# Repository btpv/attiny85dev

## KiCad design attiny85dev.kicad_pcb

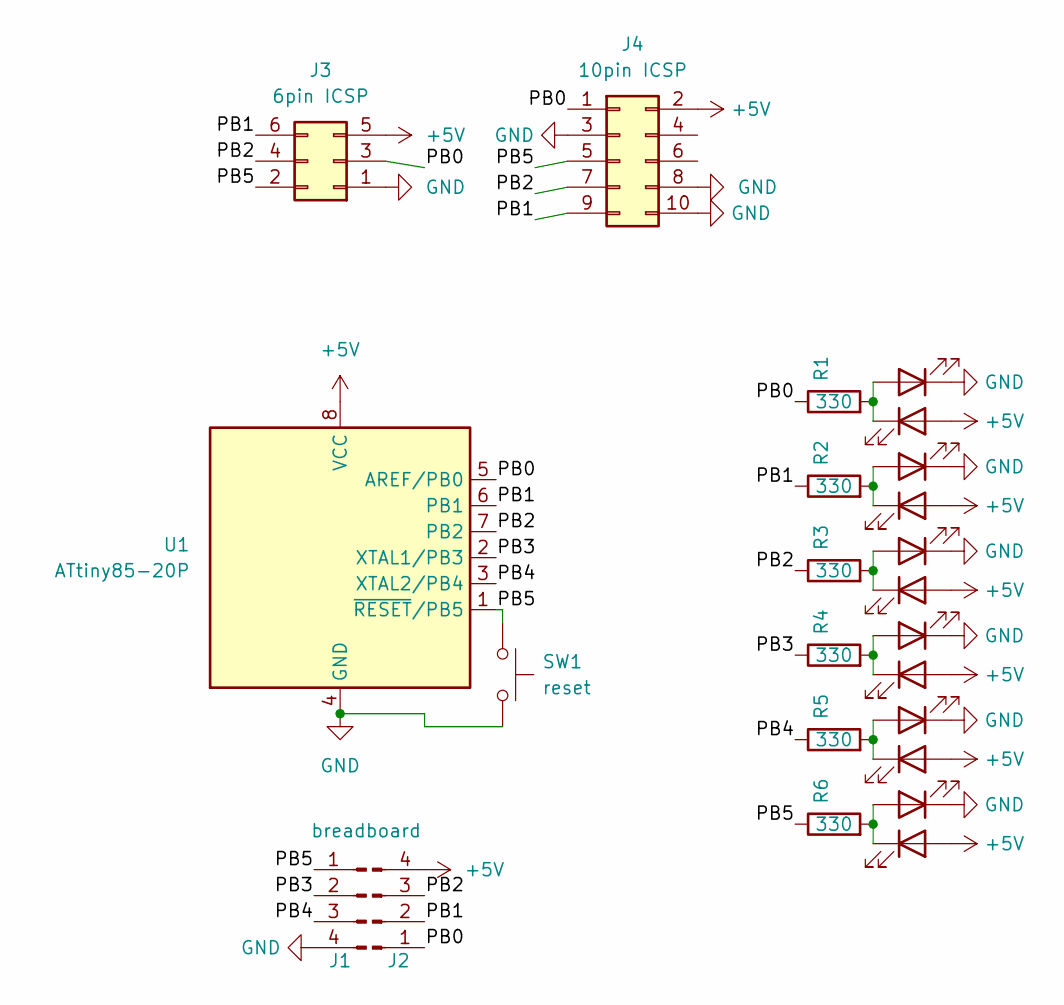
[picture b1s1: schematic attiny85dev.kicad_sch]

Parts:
D1, D2, D3, D4, D5, D6, D7, D8, D9, D10, D11, D12: LED; D_0805_2012Metric
J1: breadboard; PinHeader_1x04_P2.54mm_Vertical
J2: Conn_01x04_Pin; PinHeader_1x04_P2.54mm_Vertical
J3: 6pin ICSP; PinHeader_2x03_P2.54mm_Vertical
J4: 10pin ICSP; IDC-Header_2x05_P2.54mm_Vertical
R1, R2, R3, R4, R5, R6: 330; R_0805_2012Metric
SW1: reset; SW_PUSH_6mm
U1: ATtiny85-20P; DIP_Socket-14_W4.3mm_W5.08mm_W7.62mm_W10.16mm_W10.9mm_3M_21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

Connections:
+5V: D2.2 (A), D4.2 (A), D6.2 (A), D8.2 (A), D10.2 (A), D12.2 (A), J2.4, J3.5, J4.2, U1.8 (VCC)
/PB0: J2.1, J3.3, J4.1, R1.1, U1.5 (AREF/PB0)
/PB1: J2.2, J3.6, J4.9, R2.1, U1.6 (PB1)
/PB2: J2.3, J3.4, J4.7, R3.1, U1.7 (PB2)
/PB3: J1.2, R4.1, U1.2 (XTAL1/PB3)
/PB4: J1.3, R5.1, U1.3 (XTAL2/PB4)
/PB5: J1.1, J3.2, J4.5, R6.1, SW1.1, U1.1 (~RESET/PB5)
GND: D1.1 (K), D3.1 (K), D5.1 (K), D7.1 (K), D9.1 (K), D11.1 (K), J1.4, J3.1, J4.3, J4.8, J4.10, SW1.2, U1.4 (GND)
unnamed: D1.2 (A), D2.1 (K), R1.2
unnamed: D3.2 (A), D4.1 (K), R2.2
unnamed: D5.2 (A), D6.1 (K), R3.2
unnamed: D7.2 (A), D8.1 (K), R4.2
unnamed: D9.2 (A), D10.1 (K), R5.2
unnamed: D11.2 (A), D12.1 (K), R6.2

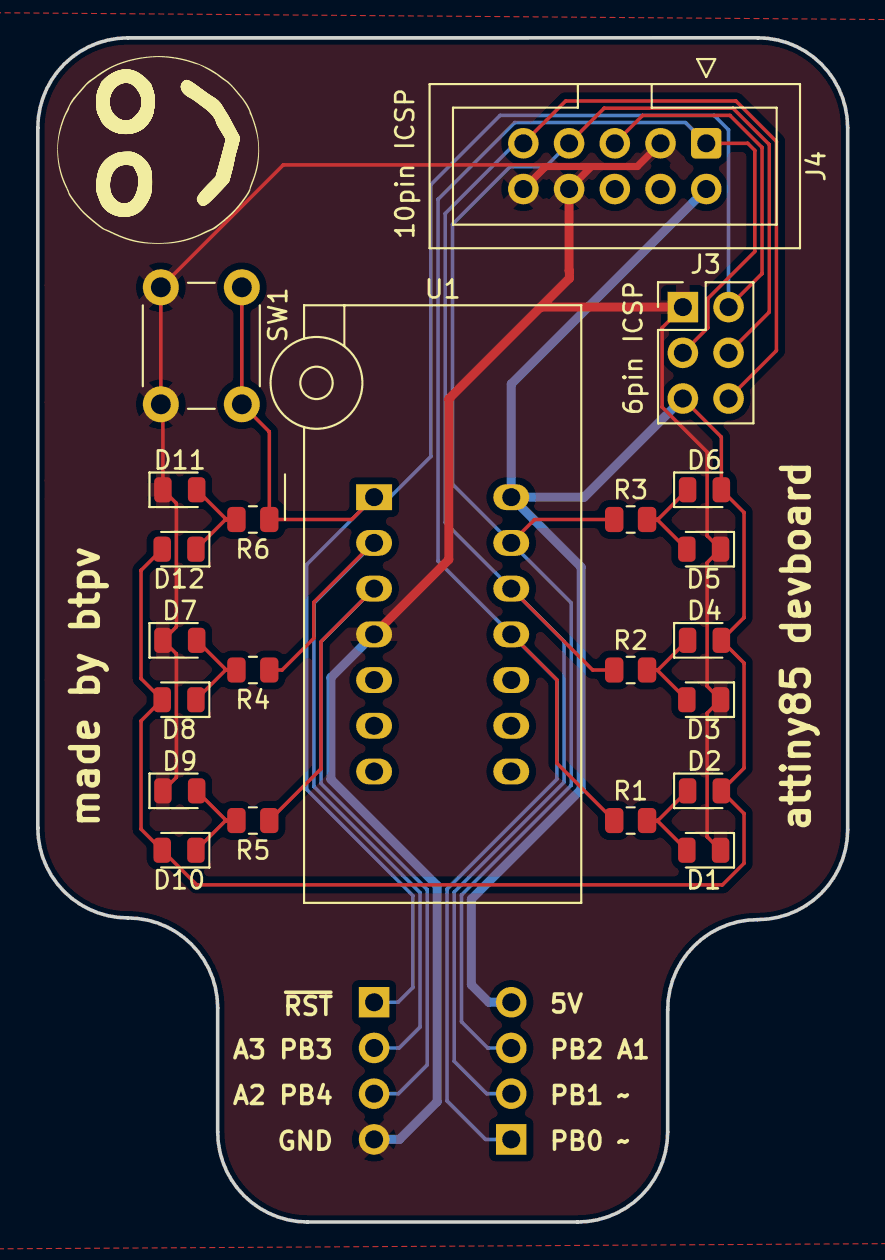
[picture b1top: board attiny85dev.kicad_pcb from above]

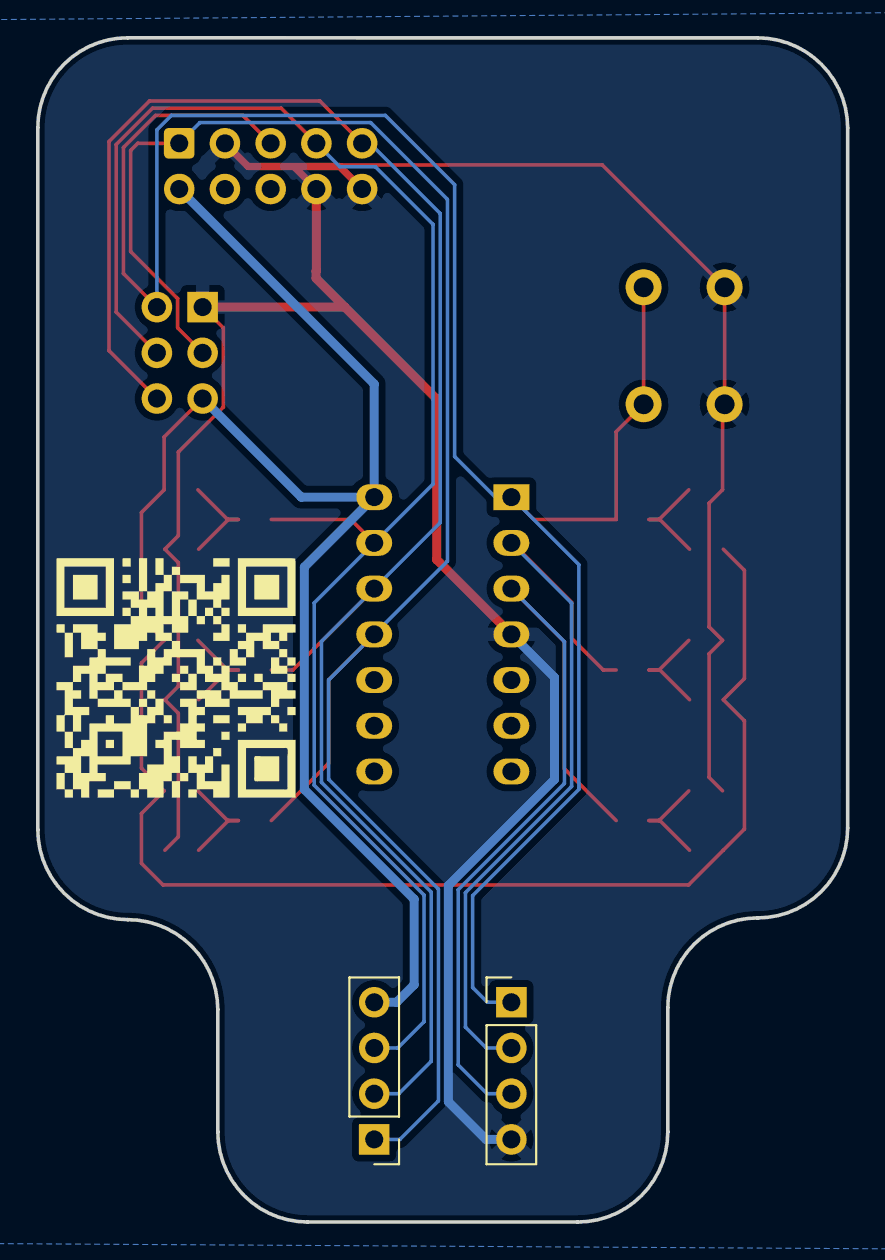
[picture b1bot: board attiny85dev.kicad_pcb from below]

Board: 2 copper layers, 45.0 x 65.8 mm, 24 parts (2 on the bottom side), 14 nets.
